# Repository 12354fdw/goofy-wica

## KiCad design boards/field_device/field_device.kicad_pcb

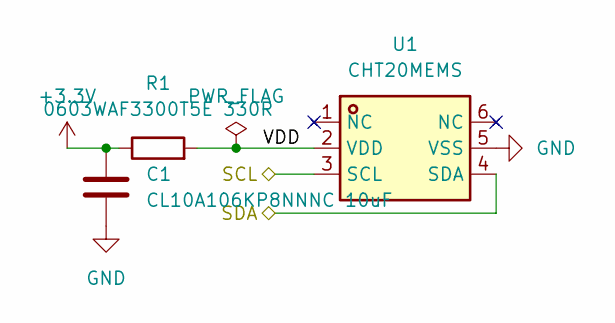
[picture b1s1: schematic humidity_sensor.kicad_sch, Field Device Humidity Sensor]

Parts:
C1: CL10A106KP8NNNC 10uF; C_0603_1608Metric_Pad1.08x0.95mm_HandSolder
R1: 0603WAF3300T5E 330R; C_0603_1608Metric
U1: CHT20MEMS; LGA-6_L3.0-W3.0-P1.00-BR; MPN CHT20MEMS; LCSC Part C26159166

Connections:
+3.3V: C1.1, R1.1; also elsewhere on the board
/MCU/SCL_bus: U1.3 (SCL); also elsewhere on the board
/MCU/SDA_bus: U1.4 (SDA); also elsewhere on the board
/humidity_sensor/VDD: R1.2, U1.2 (VDD)
GND: C1.2, U1.5 (VSS); also elsewhere on the board

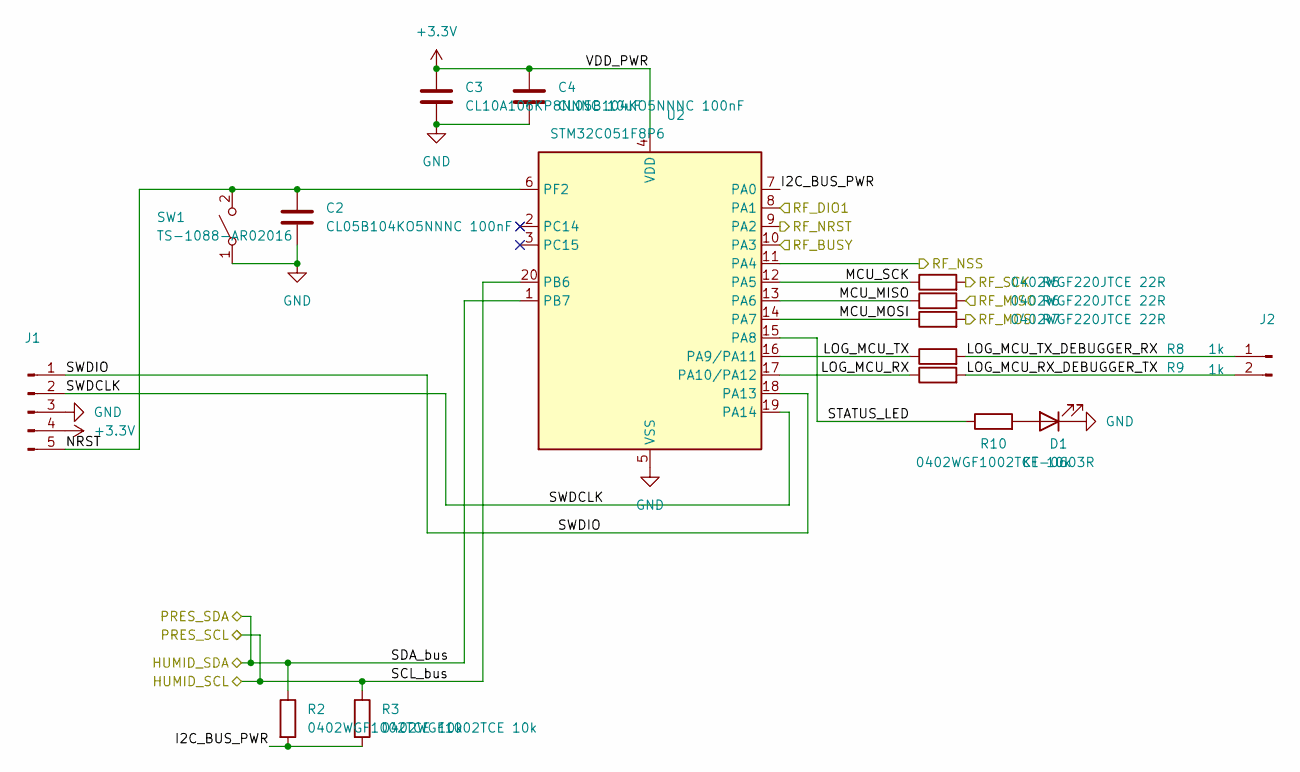
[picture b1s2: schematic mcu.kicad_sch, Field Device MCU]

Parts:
C2, C4: CL05B104KO5NNNC 100nF; C_0402_1005Metric_Pad0.74x0.62mm_HandSolder
C3: CL10A106KP8NNNC 10uF; C_0603_1608Metric_Pad1.08x0.95mm_HandSolder
D1: KT-0603R; LED_0603_1608Metric_Pad1.05x0.95mm_HandSolder
J1: PinHeader_1x05_P2.54mm_Vertical
J2: PinHeader_1x02_P2.54mm_Vertical
R2, R3, R10: 0402WGF1002TCE 10k; R_0402_1005Metric_Pad0.72x0.64mm_HandSolder
R5, R6, R7: 0402WGF220JTCE 22R; R_0402_1005Metric_Pad0.72x0.64mm_HandSolder
R8, R9: 1k; R_0402_1005Metric_Pad0.72x0.64mm_HandSolder
SW1: TS-1088-AR02016; SW-SMD_L3.9-W3.0-P4.45
U2: STM32C051F8P6; TSSOP-20_4.4x6.5mm_P0.65mm

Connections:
+3.3V: C3.1, C4.1, J1.4, U2.4 (VDD); also elsewhere on the board
/MCU/I2C_BUS_PWR: R2.2, R3.2, U2.7 (PA0)
/MCU/LOG_MCU_RX: R9.1, U2.17 (PA10/PA12)
/MCU/LOG_MCU_RX_DEBUGGER_TX: J2.2, R9.2
/MCU/LOG_MCU_TX: R8.1, U2.16 (PA9/PA11)
/MCU/LOG_MCU_TX_DEBUGGER_RX: J2.1, R8.2
/MCU/MCU_MISO: R6.1, U2.13 (PA6)
/MCU/MCU_MOSI: R7.1, U2.14 (PA7)
/MCU/MCU_SCK: R5.1, U2.12 (PA5)
/MCU/NRST: C2.1, J1.5, SW1.2 (B), U2.6 (PF2)
/MCU/RF_BUSY: U2.10 (PA3); also elsewhere on the board
/MCU/RF_DIO1: U2.8 (PA1); also elsewhere on the board
/MCU/RF_MISO: R6.2; also elsewhere on the board
/MCU/RF_MOSI: R7.2; also elsewhere on the board
/MCU/RF_NRST: U2.9 (PA2); also elsewhere on the board
/MCU/RF_NSS: U2.11 (PA4); also elsewhere on the board
/MCU/RF_SCK: R5.2; also elsewhere on the board
/MCU/SCL_bus: R3.1, U2.20 (PB6); also elsewhere on the board
/MCU/SDA_bus: R2.1, U2.1 (PB7); also elsewhere on the board
/MCU/STATUS_LED: R10.1, U2.15 (PA8)
/MCU/SWDCLK: J1.2, U2.19 (PA14)
/MCU/SWDIO: J1.1, U2.18 (PA13)
GND: C2.2, C3.2, C4.2, D1.1 (K), J1.3, SW1.1 (A), U2.5 (VSS); also elsewhere on the board
unnamed: D1.2 (A), R10.2

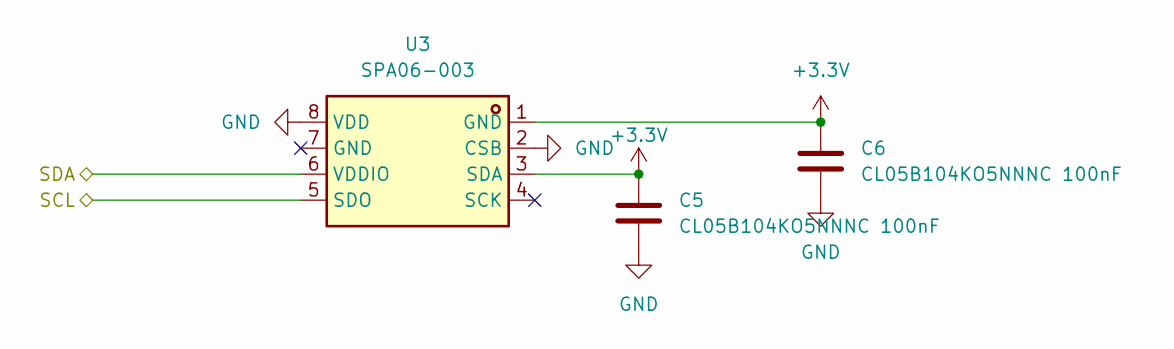
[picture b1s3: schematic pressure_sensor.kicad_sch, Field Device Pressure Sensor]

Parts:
C5, C6: CL05B104KO5NNNC 100nF; C_0402_1005Metric_Pad0.74x0.62mm_HandSolder
U3: SPA06-003; LGA-8_L2.5-W2.0-P0.65_SPA06-003; MPN SPA06-003; LCSC Part C30589048

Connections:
+3.3V: C5.1, C6.1, U3.1 (GND), U3.3 (SDA); also elsewhere on the board
/MCU/SCL_bus: U3.5 (SDO); also elsewhere on the board
/MCU/SDA_bus: U3.6 (VDDIO); also elsewhere on the board
GND: C5.2, C6.2, U3.2 (CSB), U3.8 (VDD); also elsewhere on the board

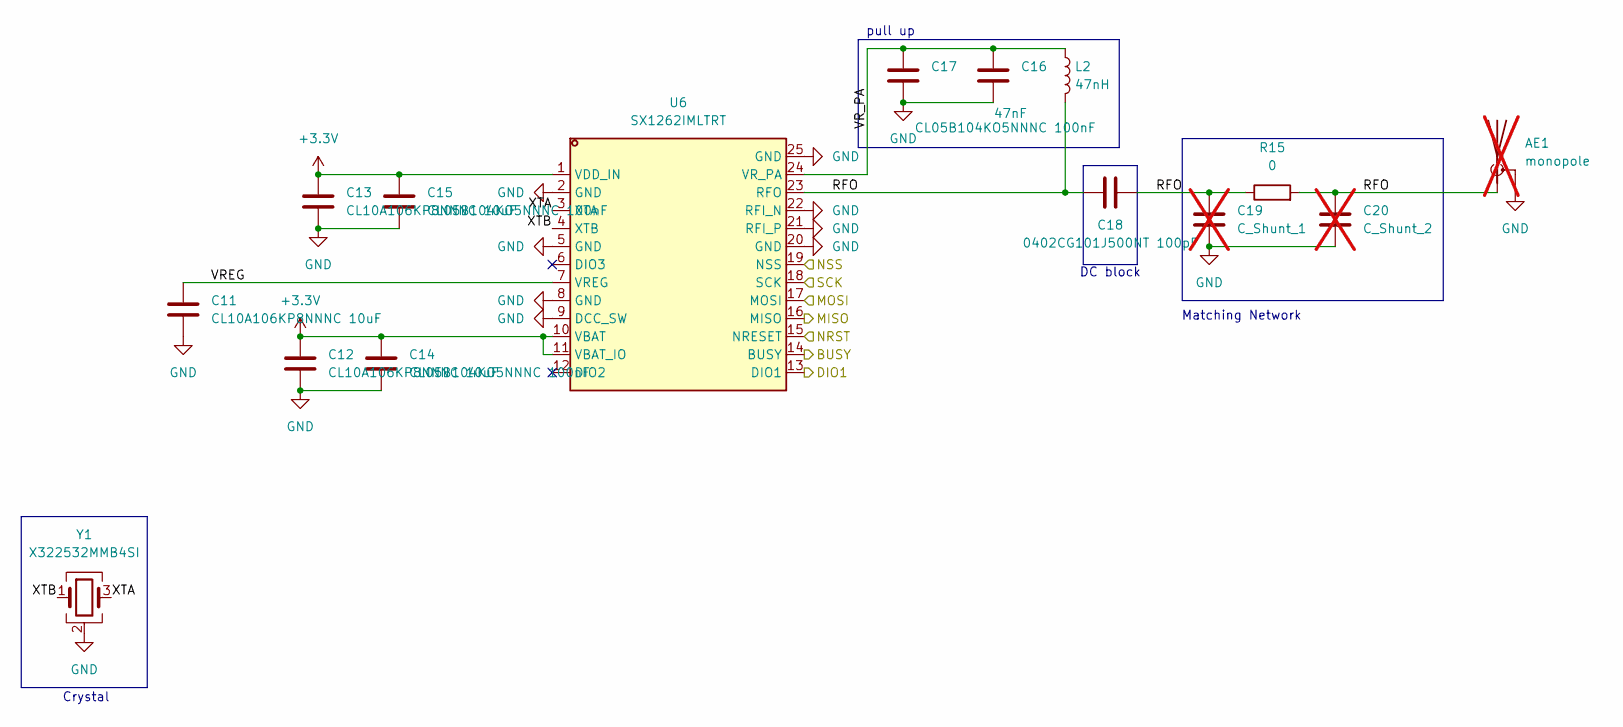
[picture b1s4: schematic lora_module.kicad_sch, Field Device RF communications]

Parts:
AE1: monopole; TI DN023 868-955MHz Antenna; not fitted
C11, C12, C13: CL10A106KP8NNNC 10uF; C_0603_1608Metric_Pad1.08x0.95mm_HandSolder
C14, C15: CL05B104KO5NNNC 100nF; C_0402_1005Metric_Pad0.74x0.62mm_HandSolder
C16: 47nF; C_0603_1608Metric
C17: CL05B104KO5NNNC 100nF; C_0402_1005Metric
C18: 0402CG101J500NT 100pF; C_0402_1005Metric_Pad0.74x0.62mm_HandSolder
C19: C_Shunt_1; C_0402_1005Metric_Pad0.74x0.62mm_HandSolder; not fitted
C20: C_Shunt_2; C_0402_1005Metric_Pad0.74x0.62mm_HandSolder; not fitted
L2: 47nH; L_0805_2012Metric_Pad1.05x1.20mm_HandSolder
R15: 0; R_0402_1005Metric_Pad0.72x0.64mm_HandSolder
U6: SX1262IMLTRT; QFN-24_L4.0-W4.0-P0.50-BL-EP2.6; MPN SX1262IMLTRT; LCSC Part C191341
Y1: X322532MMB4SI; CRYSTAL-SMD_4P-L3.2-W2.5-BL

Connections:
+3.3V: C12.1, C13.1, C14.1, C15.1, U6.1 (VDD_IN), U6.10 (VBAT), U6.11 (VBAT_IO); also elsewhere on the board
/MCU/RF_BUSY: U6.14 (BUSY); also elsewhere on the board
/MCU/RF_DIO1: U6.13 (DIO1); also elsewhere on the board
/MCU/RF_MISO: U6.16 (MISO); also elsewhere on the board
/MCU/RF_MOSI: U6.17 (MOSI); also elsewhere on the board
/MCU/RF_NRST: U6.15 (NRESET); also elsewhere on the board
/MCU/RF_NSS: U6.19 (NSS); also elsewhere on the board
/MCU/RF_SCK: U6.18 (SCK); also elsewhere on the board
/lora_module/RFO: AE1.1 (A), C18.1, C18.2, C19.1, C20.1, L2.2, R15.1, R15.2, U6.23 (RFO)
/lora_module/VREG: C11.1, U6.7 (VREG)
/lora_module/VR_PA: C16.1, C17.1, L2.1, U6.24 (VR_PA)
/lora_module/XTA: U6.3 (XTA), Y1.3
/lora_module/XTB: U6.4 (XTB), Y1.1
GND: AE1.2 (Shield), C11.2, C12.2, C13.2, C14.2, C15.2, C16.2, C17.2, C19.2, C20.2, U6.2 (GND), U6.5 (GND), U6.8 (GND), U6.9 (DCC_SW), U6.20 (GND), U6.21 (RFI_P), U6.22 (RFI_N), U6.25 (GND), Y1.2 (G), Y1.4 (G); also elsewhere on the board

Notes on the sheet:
pull up
DC block
Matching Network
Crystal

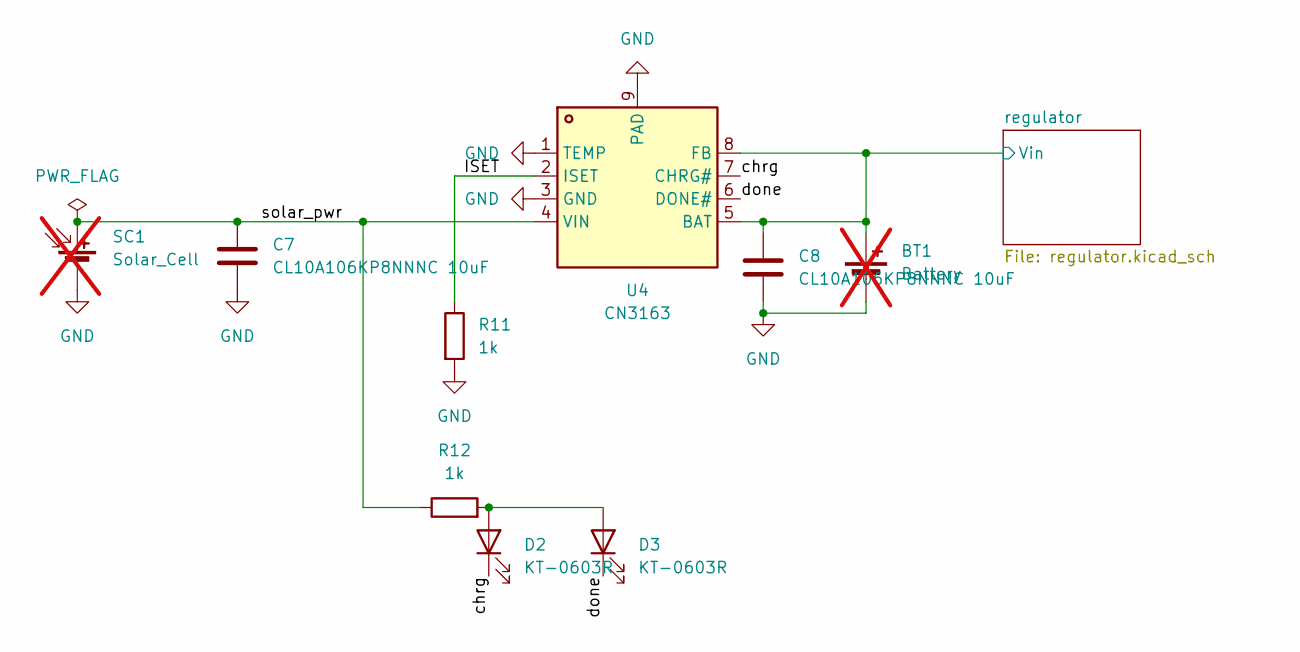
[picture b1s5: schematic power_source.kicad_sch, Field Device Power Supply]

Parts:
BT1: Battery; battery_2_smd; not fitted
C7, C8: CL10A106KP8NNNC 10uF; C_0603_1608Metric_Pad1.08x0.95mm_HandSolder
D2, D3: KT-0603R; LED_0603_1608Metric_Pad1.05x0.95mm_HandSolder
R11, R12: 1k; R_0402_1005Metric_Pad0.72x0.64mm_HandSolder
SC1: Solar_Cell; battery_2_smd; not fitted
U4: CN3163; ESOP-8_L4.9-W3.9-P1.27-LS6.0-BL-EP; MPN CN3163; LCSC Part C559031

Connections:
/power_source/ISET: R11.1, U4.2 (ISET)
/power_source/chrg: D2.1 (K), U4.7 (CHRG#)
/power_source/done: D3.1 (K), U4.6 (DONE#)
/power_source/regulator/Vin: BT1.1 (+), C8.1, U4.5 (BAT), U4.8 (FB); also elsewhere on the board
/power_source/solar_pwr: C7.1, R12.1, SC1.1 (+), U4.4 (VIN)
GND: BT1.2 (-), C7.2, C8.2, R11.2, SC1.2 (-), U4.1 (TEMP), U4.3 (GND), U4.9 (PAD); also elsewhere on the board
unnamed: D2.2 (A), D3.2 (A), R12.2

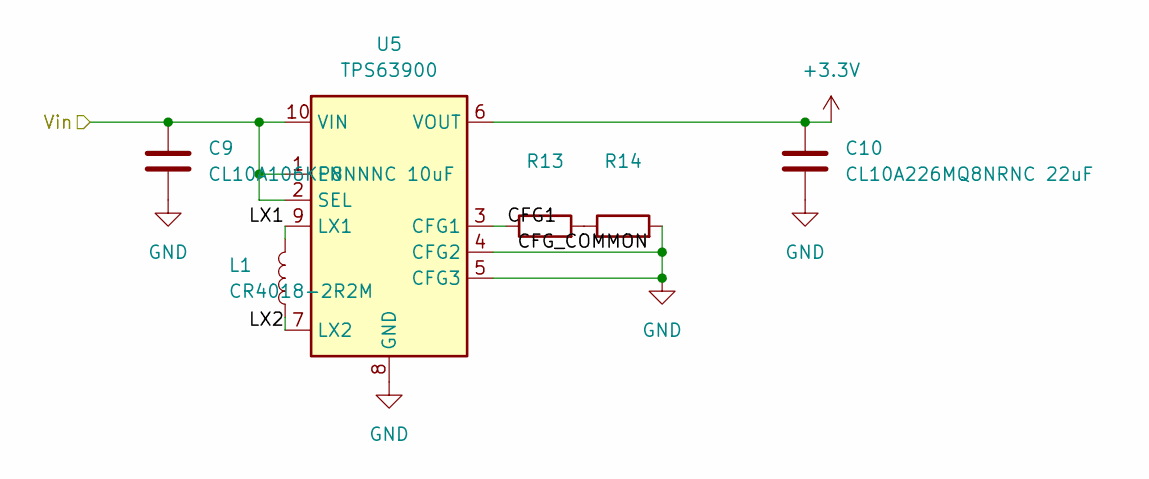
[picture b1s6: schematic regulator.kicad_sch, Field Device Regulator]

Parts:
C9: CL10A106KP8NNNC 10uF; C_0603_1608Metric_Pad1.08x0.95mm_HandSolder
C10: CL10A226MQ8NRNC 22uF; C_0603_1608Metric_Pad1.08x0.95mm_HandSolder
L1: CR4018-2R2M; IND-SMD_L4.0-W4.0
R13: 0603WAF3601T5E; R_0603_1608Metric
R14: 0603WAF3302T5E; R_0603_1608Metric
U5: TPS63900; WSON-10-1EP_2.5x2.5mm_P0.5mm_EP1.2x2mm_ThermalVias

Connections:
+3.3V: C10.1, U5.6 (VOUT); also elsewhere on the board
/power_source/regulator/CFG1: R13.1, U5.3 (CFG1)
/power_source/regulator/LX1: L1.2, U5.9 (LX1)
/power_source/regulator/LX2: L1.1, U5.7 (LX2)
/power_source/regulator/Vin: C9.1, U5.1 (EN), U5.2 (SEL), U5.10 (VIN); also elsewhere on the board
GND: C9.2, C10.2, R14.2, U5.4 (CFG2), U5.5 (CFG3), U5.8 (GND), U5.11 (GND); also elsewhere on the board
unnamed: R13.2, R14.1

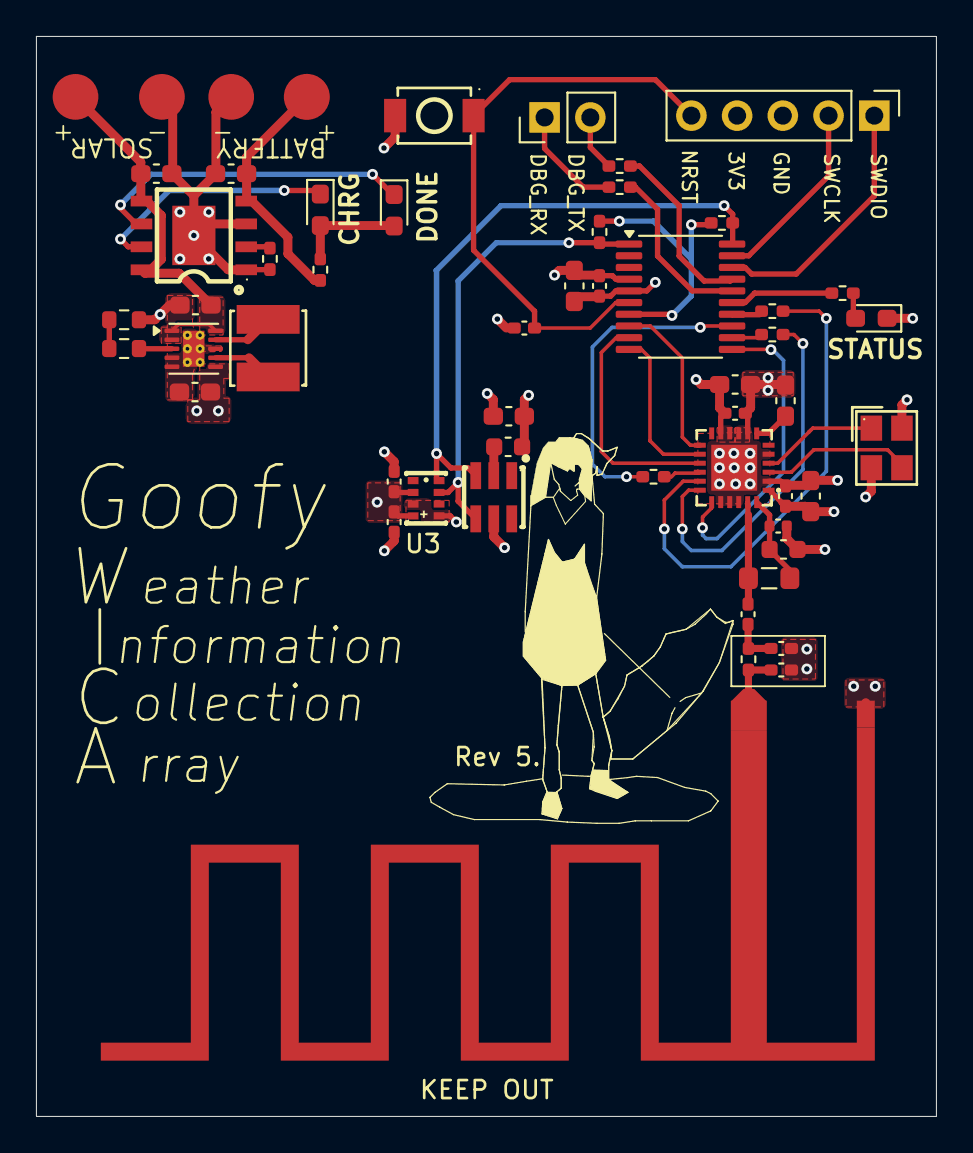
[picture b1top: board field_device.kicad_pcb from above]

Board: 4 copper layers, 50.0 x 60.0 mm, 52 parts (0 on the bottom side), 40 nets.

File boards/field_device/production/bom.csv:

Designator,Footprint,Quantity,Value,LCSC Part #
"C1, C11, C12, C13, C3, C7, C8, C9",0603,8,10uF,
C10,0603,1,22uF,
"C14, C15, C2, C4, C5, C6",0402,6,100nF,
C16,1206,1,47nF C0G,
"C17, C18",0402,2,100p C0G,
"D1, D2, D3",0603,3,KT-0603R,
J1,PinHeader_1x05_P2.54mm_Vertical,1,~,
J2,PinHeader_1x02_P2.54mm_Vertical,1,~,
L1,IND-SMD_L4.0-W4.0,1,CR4018-2R2M,C520302
L2,0402,1,47nH,
R1,0402,1,330R,
"R10, R2, R3",0402,3,10k,
"R11, R12, R8, R9",0402,4,1k,
R13,0603,1,0603WAF3601T5E,
R14,0603,1,0603WAF3302T5E,
R15,0402,1,0,
"R5, R6, R7",0402,3,22R,
SW1,SW-SMD_L3.9-W3.0-P4.45,1,TS-1088-AR02016,C720477
U1,LGA-6_L3.0-W3.0-P1.00-BR,1,CHT20MEMS,C26159166
U2,TSSOP-20_4.4x6.5mm_P0.65mm,1,STM32C051F8P6,
U3,LGA-8_L2.5-W2.0-P0.65_SPA06-003,1,SPA06-003,C30589048
U4,ESOP-8_L4.9-W3.9-P1.27-LS6.0-BL-EP,1,CN3163,C559031
U5,WSON-10-1EP_2.5x2.5mm_P0.5mm_EP1.2x2mm_ThermalVias,1,TPS63900,
U6,QFN-24_L4.0-W4.0-P0.50-BL-EP2.6,1,SX1262IMLTRT,C191341
Y1,CRYSTAL-SMD_4P-L3.2-W2.5-BL,1,X322532MMB4SI,C113671
